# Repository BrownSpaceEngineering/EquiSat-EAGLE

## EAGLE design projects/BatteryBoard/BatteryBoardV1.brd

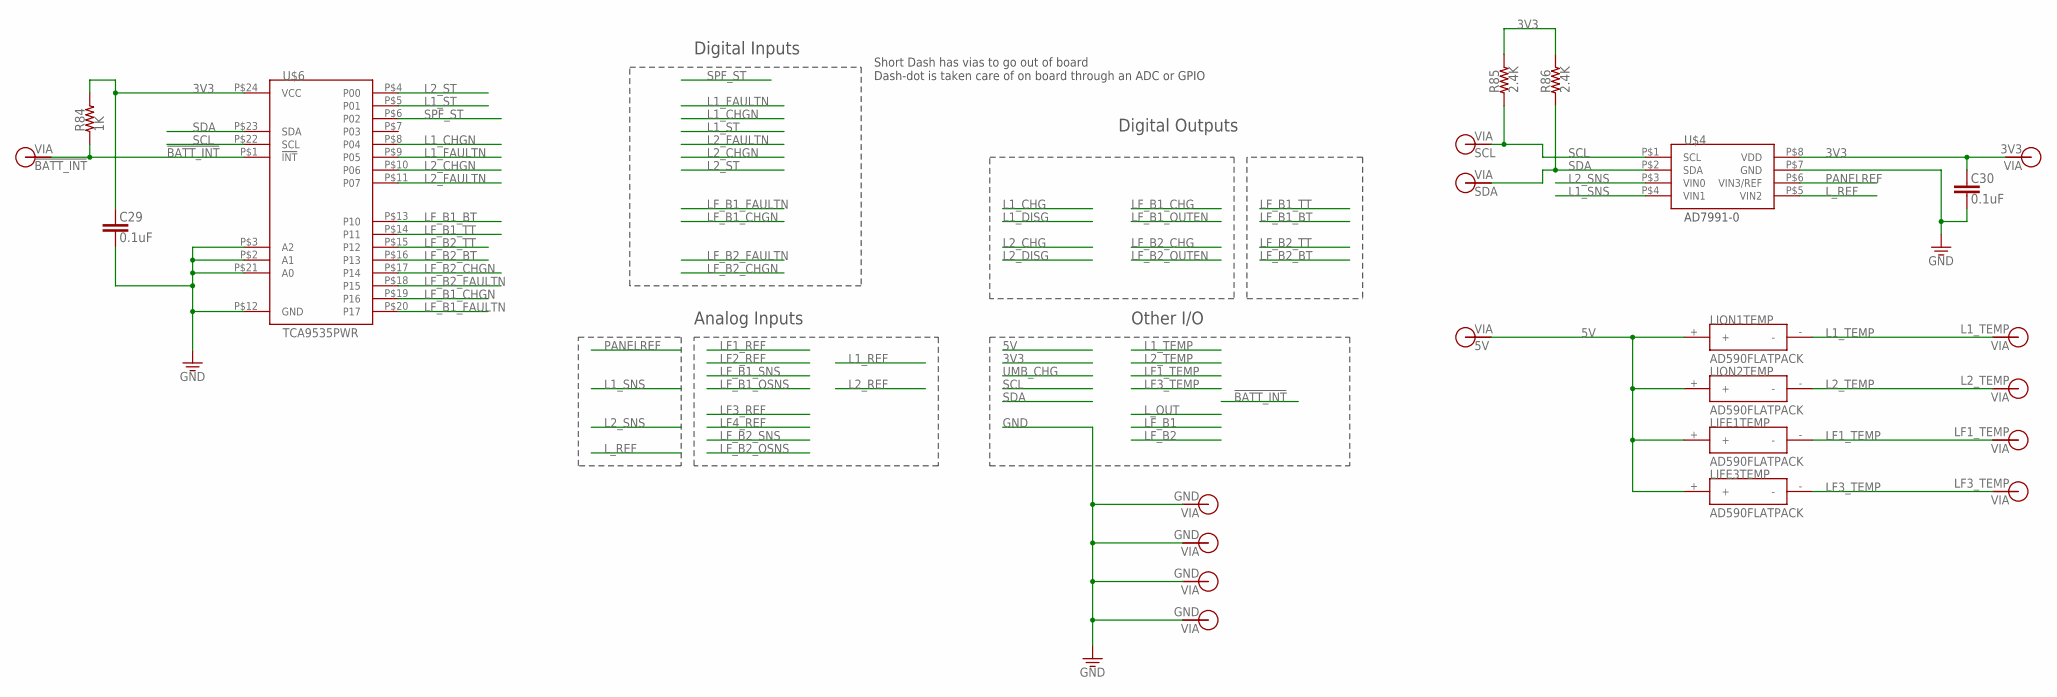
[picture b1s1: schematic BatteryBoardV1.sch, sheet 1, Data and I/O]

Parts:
C29, C30: 0.1uF; 0805
LIFE1TEMP, LIFE3TEMP: AD590FLATPACK; FLATPACK
LION1TEMP, LION2TEMP: AD590FLATPACK; FLATPACK
R84: 1K; 0805
R85, R86: 2.4K; 0805
U$4: AD7991-0; SOT-23-8
U$6: TCA9535PWR; TSSOP-24
V9: 5V; VIA-60MIL
V11: !BATT_INT!; VIA-60MIL
V12: GND; VIA-60MIL-SQ
V13, V22, V23: GND; VIA-120MIL
V24: L1_TEMP; VIA-60MIL
V32: L2_TEMP; VIA-60MIL
V37: LF1_TEMP; VIA-60MIL
V50: LF3_TEMP; VIA-60MIL
V51: 3V3; VIA-60MIL
V52: SCL; VIA-60MIL
V53: SDA; VIA-60MIL

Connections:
3V3: C29.1, C30.1, R84.2, R85.2, R86.2, U$4.P$8 (VDD), U$6.P$24 (VCC), V51.P$1; also elsewhere on the board
5V: LIFE1TEMP.+, LIFE3TEMP.+, LION1TEMP.+, LION2TEMP.+, V9.P$1
!BATT_INT!: R84.1, U$6.P$1 (!INT!), V11.P$1
GND: C29.2, C30.2, U$4.P$7 (GND), U$6.P$2 (A1), U$6.P$3 (A2), U$6.P$12 (GND), U$6.P$21 (A0), V12.P$1, V13.P$1, V22.P$1, V23.P$1; also elsewhere on the board
L1_CHGN: U$6.P$8 (P04); also elsewhere on the board
L1_FAULTN: U$6.P$9 (P05); also elsewhere on the board
L1_SNS: U$4.P$4 (VIN1); also elsewhere on the board
L1_ST: U$6.P$5 (P01); also elsewhere on the board
L1_TEMP: LION1TEMP.-, V24.P$1
L2_CHGN: U$6.P$10 (P06); also elsewhere on the board
L2_FAULTN: U$6.P$11 (P07); also elsewhere on the board
L2_SNS: U$4.P$3 (VIN0); also elsewhere on the board
L2_ST: U$6.P$4 (P00); also elsewhere on the board
L2_TEMP: LION2TEMP.-, V32.P$1
LF1_TEMP: LIFE1TEMP.-, V37.P$1
LF3_TEMP: LIFE3TEMP.-, V50.P$1
LF_B1_BT: U$6.P$13 (P10); also elsewhere on the board
LF_B1_CHGN: U$6.P$19 (P16); also elsewhere on the board
LF_B1_FAULTN: U$6.P$20 (P17); also elsewhere on the board
LF_B1_TT: U$6.P$14 (P11); also elsewhere on the board
LF_B2_BT: U$6.P$16 (P13); also elsewhere on the board
LF_B2_CHGN: U$6.P$17 (P14); also elsewhere on the board
LF_B2_FAULTN: U$6.P$18 (P15); also elsewhere on the board
LF_B2_TT: U$6.P$15 (P12); also elsewhere on the board
L_REF: U$4.P$5 (VIN2); also elsewhere on the board
PANELREF: U$4.P$6 (VIN3/REF); also elsewhere on the board
SCL: R85.1, U$4.P$1 (SCL), U$6.P$22 (SCL), V52.P$1
SDA: R86.1, U$4.P$2 (SDA), U$6.P$23 (SDA), V53.P$1
SPF_ST: U$6.P$6 (P02); also elsewhere on the board

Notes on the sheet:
Digital Inputs
Digital Outputs
Analog Inputs
Other I/O
Short Dash has vias to go out of board Dash-dot is taken care of on board through an ADC or GPIO

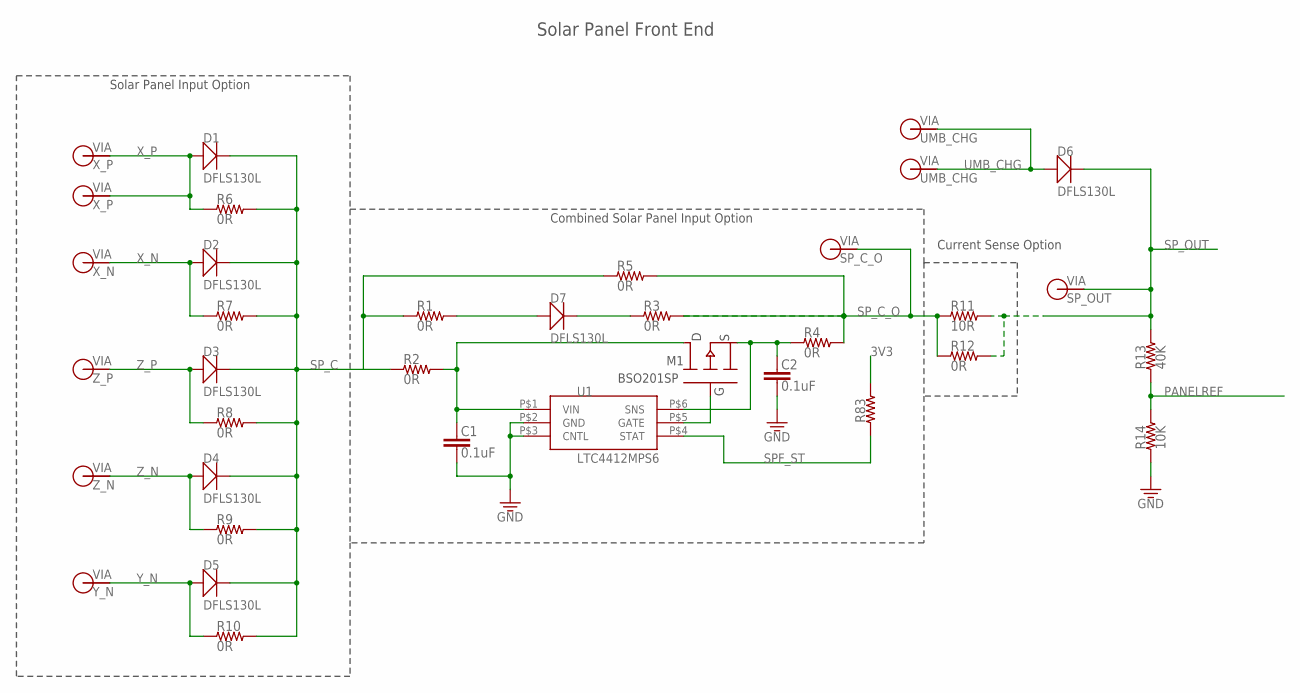
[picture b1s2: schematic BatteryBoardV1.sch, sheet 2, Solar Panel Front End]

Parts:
C1, C2: 0.1uF; 0805
D1, D2, D3, D4, D5, D6, D7: DFLS130L; PWRDI-123
M1: BSO201SP; SO-8
R1, R2, R3, R4, R5, R6, R7, R8, R9, R10, R12: 0R; 0805
R11: 10R; 0805
R13: 40K; 0805
R14: 10K; 0805
R83: RES0805; 0805
U1: LTC4412MPS6; TSOT23-6
V1: UMB_CHG; VIA-60MIL
V2: X_P; VIA-60MIL
V3: X_N; VIA-60MIL
V4: Z_P; VIA-60MIL
V5: Z_N; VIA-60MIL
V6: Y_N; VIA-60MIL
V7: SP_C_O; VIA-60MIL-SQ
V8: SP_OUT; VIA-60MIL-SQ
V39: UMB_CHG; VIA-60MIL-SQ
V49: X_P; VIA-60MIL-SQ

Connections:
3V3: R83.2; also elsewhere on the board
GND: C1.2, C2.2, R14.1, U1.P$2 (GND), U1.P$3 (CNTL); also elsewhere on the board
unnamed: M1.P$4 (G), U1.P$5 (GATE)
unnamed: C2.1, M1.P$1 (S), M1.P$2 (S), M1.P$3 (S), R4.1, U1.P$6 (SNS)
unnamed: D7.A, R1.2
unnamed: D7.C, R3.1
unnamed: C1.1, M1.P$5 (D), M1.P$6 (D), M1.P$7 (D), M1.P$8 (D), R2.2, U1.P$1 (VIN)
PANELREF: R13.1, R14.2; also elsewhere on the board
SPF_ST: R83.1, U1.P$4 (STAT); also elsewhere on the board
SP_C: D1.C, D2.C, D3.C, D4.C, D5.C, R1.1, R2.1, R5.1, R6.2, R7.2, R8.2, R9.2, R10.2
SP_C_O: R3.2, R4.2, R5.2, R11.1, R12.1, V7.P$1
SP_OUT: D6.C, R11.2, R12.2, R13.2, V8.P$1; also elsewhere on the board
UMB_CHG: D6.A, V1.P$1, V39.P$1
X_N: D2.A, R7.1, V3.P$1
X_P: D1.A, R6.1, V2.P$1, V49.P$1
Y_N: D5.A, R10.1, V6.P$1
Z_N: D4.A, R9.1, V5.P$1
Z_P: D3.A, R8.1, V4.P$1

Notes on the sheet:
Solar Panel Input Option
Combined Solar Panel Input Option
Current Sense Option
Solar Panel Front End

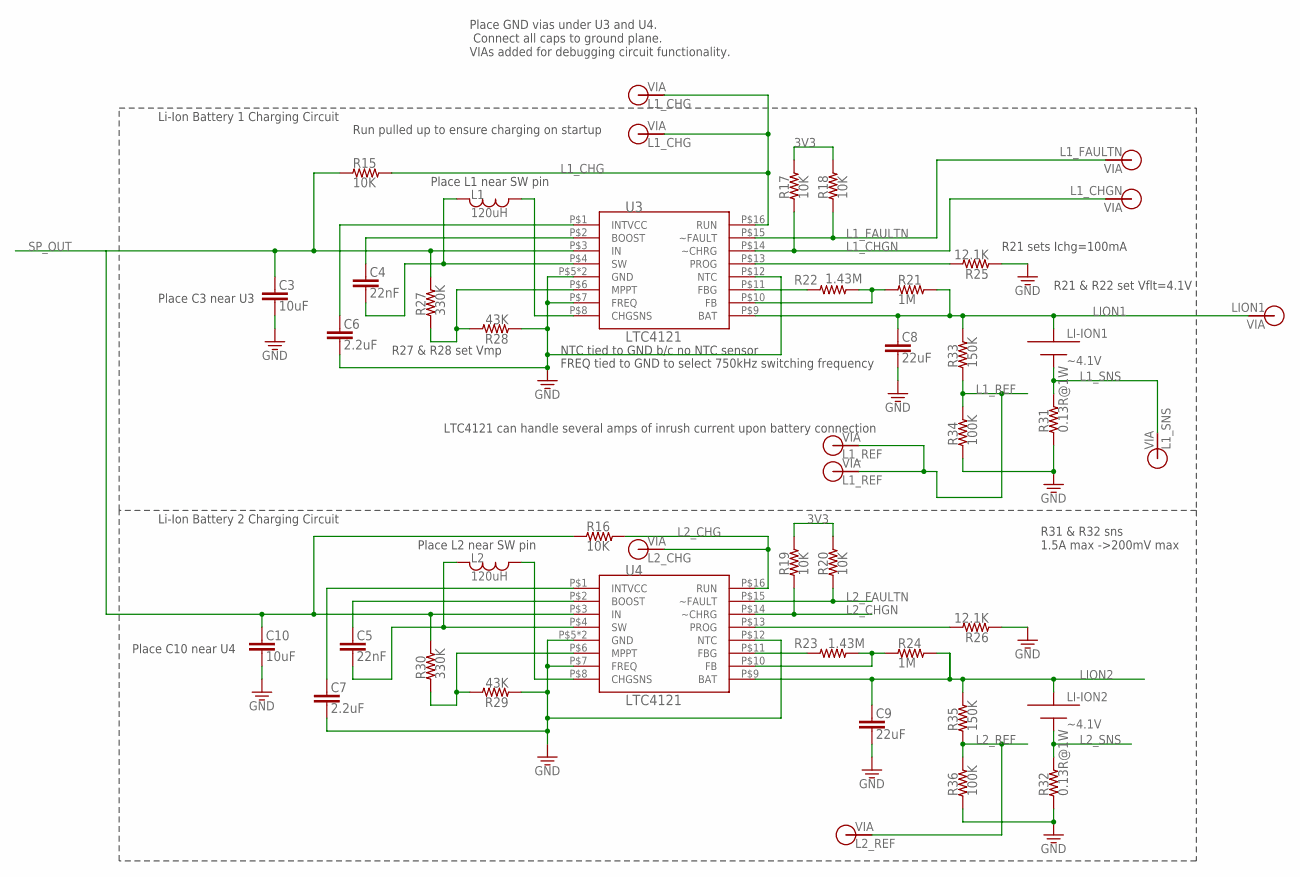
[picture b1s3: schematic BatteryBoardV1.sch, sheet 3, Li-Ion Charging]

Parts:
C3, C10: 10uF; 0805
C4, C5: 22nF; 0805
C6, C7: 2.2uF; 0805
C8, C9: 22uF; 0805
L1, L2: 120uH; 1812
LI-ION1, LI-ION2: ~4.1V; EQUISAT-BATTERY-VA
R15, R16, R17, R18, R19, R20: 10K; 0805
R21, R24: 1M; 0805
R22, R23: 1.43M; 0805
R25, R26: 12.1K; 0805
R27, R30: 330K; 0805
R28, R29: 43K; 0805
R31, R32: 0.13R@1W; 1210
R33, R35: 150K; 0805
R34, R36: 100K; 0805
U3, U4: LTC4121; QFN-16-PAD
V10: L1_CHG; VIA-60MIL
V25: L1_REF; VIA-60MIL
V29: L2_REF; VIA-60MIL
V33: L2_CHG; VIA-60MIL
V40: L1_CHG; VIA-60MIL-SQ
V41: L1_FAULTN; VIA-60MIL-SQ
V42: L1_CHGN; VIA-60MIL-SQ
V43: L1_SNS; VIA-60MIL-SQ
V44: L1_REF; VIA-60MIL-SQ
V45: LION1; VIA-60MIL-SQ

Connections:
3V3: R17.2, R18.2, R19.2, R20.2; also elsewhere on the board
GND: C3.2, C6.2, C7.2, C8.2, C9.2, C10.2, R25.1, R26.1, R28.1, R29.1, R31.P$1 (1), R32.P$1 (1), R34.1, R36.1, U3.P$5 (GND), U3.P$7 (FREQ), U3.P$12 (NTC), U3.P$17 (GND), U4.P$5 (GND), U4.P$7 (FREQ), U4.P$12 (NTC), U4.P$17 (GND); also elsewhere on the board
L1_CHG: R15.2, U3.P$16 (RUN), V10.P$1, V40.P$1
L1_CHGN: R17.1, U3.P$14 (~CHRG), V42.P$1; also elsewhere on the board
L1_FAULTN: R18.1, U3.P$15 (~FAULT), V41.P$1; also elsewhere on the board
L1_REF: R33.1, R34.2, V25.P$1, V44.P$1
L1_SNS: LI-ION1.MINUS, R31.P$2 (2), V43.P$1; also elsewhere on the board
L2_CHG: R16.2, U4.P$16 (RUN), V33.P$1
L2_CHGN: R19.1, U4.P$14 (~CHRG); also elsewhere on the board
L2_FAULTN: R20.1, U4.P$15 (~FAULT); also elsewhere on the board
L2_REF: R35.1, R36.2, V29.P$1
L2_SNS: LI-ION2.MINUS, R32.P$2 (2); also elsewhere on the board
LION1: C8.1, LI-ION1.PLUS, R21.2, R33.2, U3.P$9 (BAT), V45.P$1; also elsewhere on the board
LION2: C9.1, LI-ION2.PLUS, R24.2, R35.2, U4.P$9 (BAT); also elsewhere on the board
unnamed: C4.2, L1.P$1, U3.P$4 (SW)
unnamed: C4.1, U3.P$2 (BOOST)
unnamed: C5.1, U4.P$2 (BOOST)
unnamed: C5.2, L2.P$1, U4.P$4 (SW)
unnamed: C7.1, U4.P$1 (INTVCC)
unnamed: C6.1, U3.P$1 (INTVCC)
unnamed: R23.1, U4.P$11 (FBG)
unnamed: R23.2, R24.1, U4.P$10 (FB)
unnamed: R22.1, U3.P$11 (FBG)
unnamed: R21.1, R22.2, U3.P$10 (FB)
unnamed: L1.P$2, U3.P$8 (CHGSNS)
unnamed: R25.2, U3.P$13 (PROG)
unnamed: R26.2, U4.P$13 (PROG)
unnamed: R29.2, R30.1, U4.P$6 (MPPT)
unnamed: R27.1, R28.2, U3.P$6 (MPPT)
unnamed: L2.P$2, U4.P$8 (CHGSNS)
SP_OUT: C3.1, C10.1, R15.1, R16.1, R27.2, R30.2, U3.P$3 (IN), U4.P$3 (IN); also elsewhere on the board

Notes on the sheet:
FREQ tied to GND to select 750kHz switching frequency
R21 sets Ichg=100mA
R21 & R22 set Vflt=4.1V
R27 & R28 set Vmp
Place C3 near U3
Place C10 near U4
Place L2 near SW pin
Place L1 near SW pin
Place GND vias under U3 and U4. Connect all caps to ground plane. VIAs added for debugging circuit functionality.
Li-Ion Battery 1 Charging Circuit
Li-Ion Battery 2 Charging Circuit
Run pulled up to ensure charging on startup
NTC tied to GND b/c no NTC sensor
R31 & R32 sns 1.5A max ->200mV max
LTC4121 can handle several amps of inrush current upon battery connection

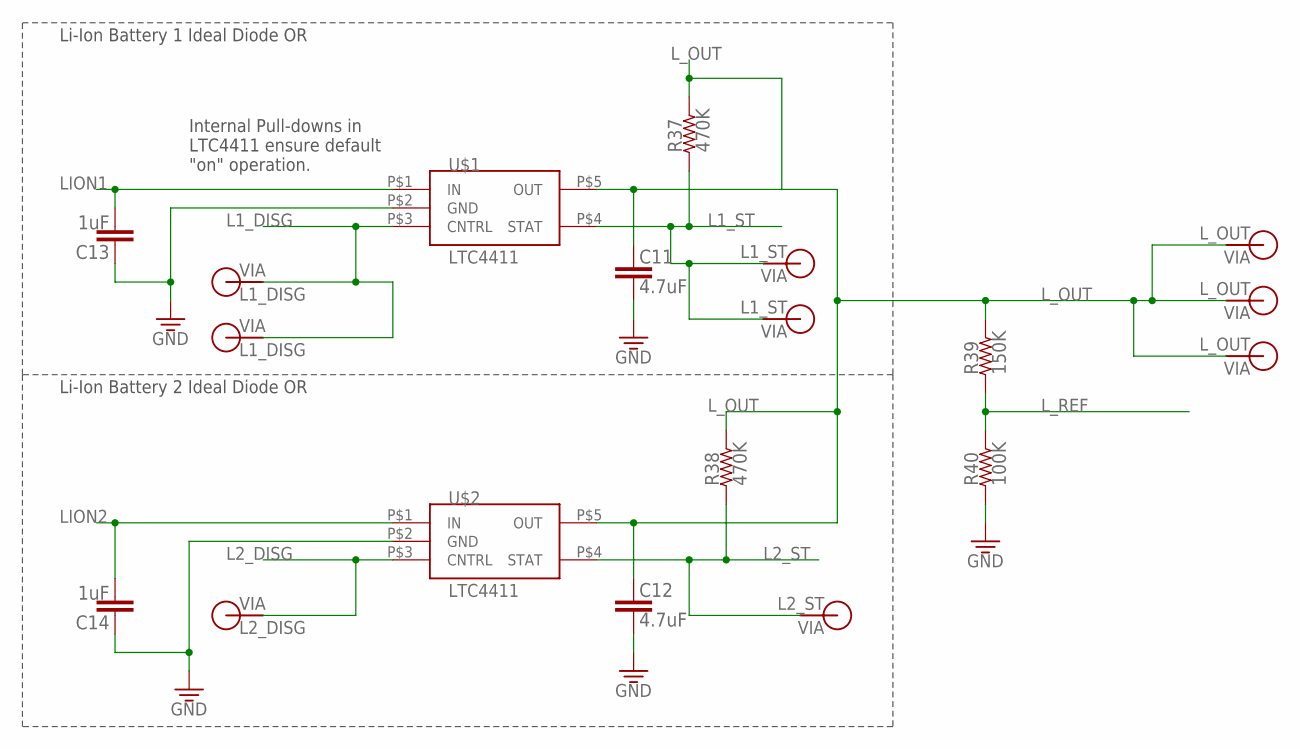
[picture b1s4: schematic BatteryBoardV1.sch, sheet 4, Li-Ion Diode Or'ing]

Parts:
C11, C12: 4.7uF; 0805
C13, C14: 1uF; 0805
R37, R38: 470K; 0805
R39: 150K; 0805
R40: 100K; 0805
U$1, U$2: LTC4411; TSOT23-5
V30, V54: L_OUT; VIA-120MIL
V34: L1_DISG; VIA-60MIL
V35: L2_DISG; VIA-60MIL
V36: L1_ST; VIA-60MIL
V38: L2_ST; VIA-60MIL
V46: L1_DISG; VIA-60MIL-SQ
V47: L1_ST; VIA-60MIL-SQ
V48: L_OUT; VIA-60MIL-SQ

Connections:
GND: C11.2, C12.2, C13.1, C14.1, R40.1, U$1.P$2 (GND), U$2.P$2 (GND); also elsewhere on the board
L1_DISG: U$1.P$3 (CNTRL), V34.P$1, V46.P$1
L1_ST: R37.1, U$1.P$4 (STAT), V36.P$1, V47.P$1; also elsewhere on the board
L2_DISG: U$2.P$3 (CNTRL), V35.P$1
L2_ST: R38.1, U$2.P$4 (STAT), V38.P$1; also elsewhere on the board
LION1: C13.2, U$1.P$1 (IN); also elsewhere on the board
LION2: C14.2, U$2.P$1 (IN); also elsewhere on the board
L_OUT: C11.1, C12.1, R37.2, R38.2, R39.2, U$1.P$5 (OUT), U$2.P$5 (OUT), V30.P$1, V48.P$1, V54.P$1
L_REF: R39.1, R40.2; also elsewhere on the board

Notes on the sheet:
Internal Pull-downs in LTC4411 ensure default "on" operation.
Li-Ion Battery 1 Ideal Diode OR
Li-Ion Battery 2 Ideal Diode OR

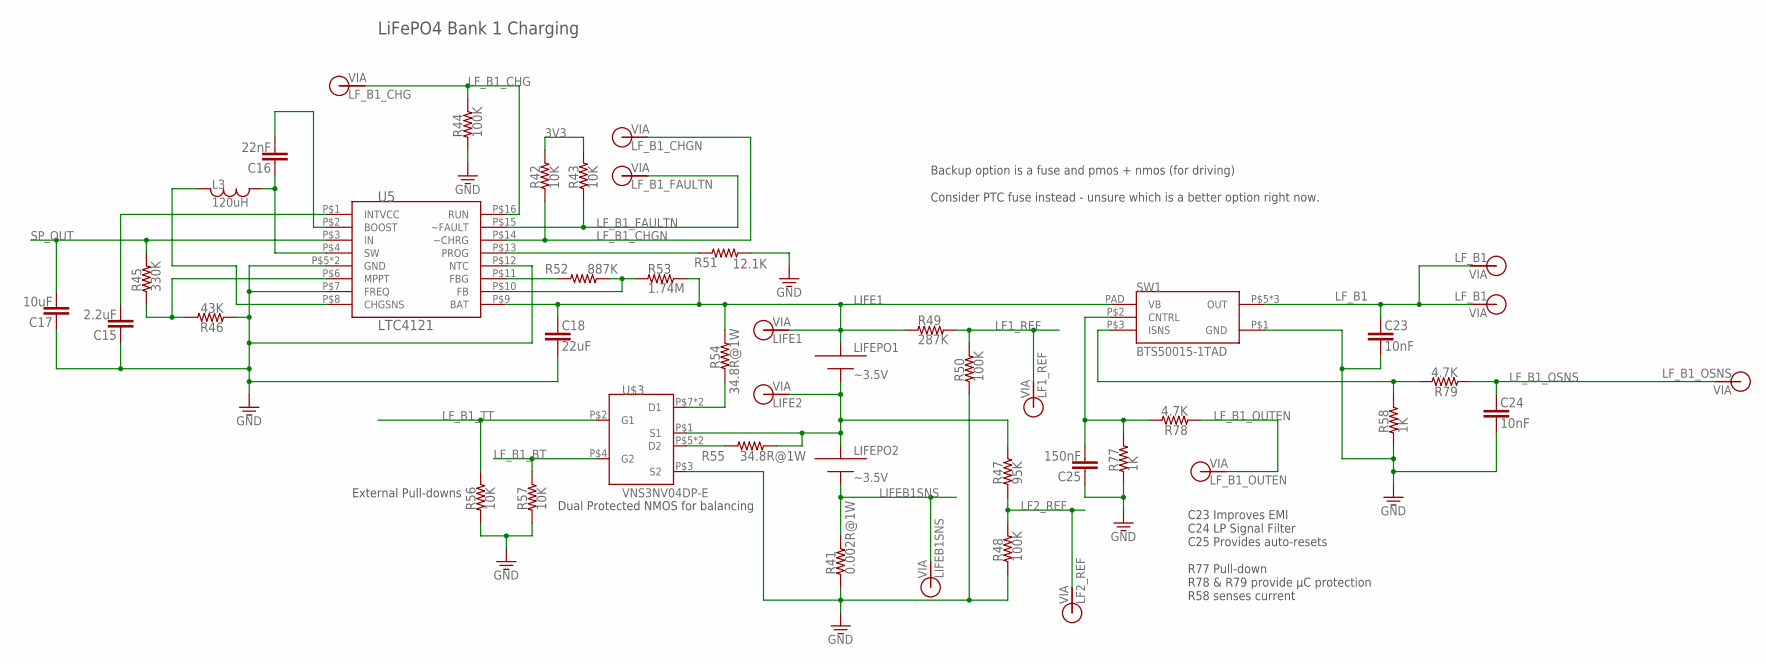
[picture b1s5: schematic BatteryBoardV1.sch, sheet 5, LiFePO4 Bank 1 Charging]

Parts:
C15: 2.2uF; 0805
C16: 22nF; 0805
C17: 10uF; 0805
C18: 22uF; 0805
C23, C24: 10nF; 0805
C25: 150nF; 0805
L3: 120uH; 1812
LIFEPO1: ~3.5V; EQUISAT-BATTERY-VA
LIFEPO2: ~3.5V; EQUISAT-BATTERY-VB
R41: 0.002R@1W; 1210
R42, R43, R56, R57: 10K; 0805
R44, R48, R50: 100K; 0805
R45: 330K; 0805
R46: 43K; 0805
R47: 95K; 0805
R49: 287K; 0805
R51: 12.1K; 0805
R52: 887K; 0805
R53: 1.74M; 0805
R54, R55: 34.8R@1W; 1210
R58, R77: 1K; 0805
R78, R79: 4.7K; 0805
SW1: BTS50015-1TAD; TO-263-7-8
U5: LTC4121; QFN-16-PAD
U$3: VNS3NV04DP-E; SO-8
V14: LIFEB1SNS; VIA-60MIL
V15: LF_B1_CHG; VIA-60MIL
V16: LIFE2; VIA-60MIL-SQ
V17: LIFE1; VIA-60MIL-SQ
V18: LF_B1_CHGN; VIA-60MIL
V19: LF_B1_FAULTN; VIA-60MIL
V20: LF_B1_OUTEN; VIA-60MIL
V21, V26: LF_B1; VIA-120MIL
V31: LF_B1_OSNS; VIA-60MIL
V58: LF1_REF; VIA-60MIL
V59: LF2_REF; VIA-60MIL

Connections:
3V3: R42.2, R43.2; also elsewhere on the board
GND: C15.1, C17.1, C18.2, C23.2, C24.2, C25.1, R41.P$1 (1), R44.1, R46.1, R48.1, R50.1, R51.2, R56.1, R57.1, R58.1, R77.1, SW1.P$1 (GND), U5.P$5 (GND), U5.P$7 (FREQ), U5.P$12 (NTC), U5.P$17 (GND), U$3.P$3 (S2); also elsewhere on the board
LF1_REF: R49.2, R50.2, V58.P$1
LF2_REF: R47.1, R48.2, V59.P$1
LF_B1: C23.1, SW1.P$5 (OUT), SW1.P$6 (OUT), SW1.P$7 (OUT), V21.P$1, V26.P$1
LF_B1_BT: R57.2, U$3.P$4 (G2); also elsewhere on the board
LF_B1_CHG: R44.2, U5.P$16 (RUN), V15.P$1
LF_B1_CHGN: R42.1, U5.P$14 (~CHRG), V18.P$1; also elsewhere on the board
LF_B1_FAULTN: R43.1, U5.P$15 (~FAULT), V19.P$1; also elsewhere on the board
LF_B1_OSNS: C24.1, R79.1, V31.P$1
LF_B1_OUTEN: R78.1, V20.P$1
LF_B1_TT: R56.2, U$3.P$2 (G1); also elsewhere on the board
LIFE1: C18.1, LIFEPO1.PLUS, R49.1, R53.2, R54.P$2 (2), SW1.PAD (VB), U5.P$9 (BAT), V17.P$1
LIFE2: LIFEPO1.MINUS, LIFEPO2.PLUS, R47.2, R55.P$1 (1), U$3.P$1 (S1), V16.P$1
LIFEB1SNS: LIFEPO2.MINUS, R41.P$2 (2), V14.P$1
unnamed: R51.1, U5.P$13 (PROG)
unnamed: R54.P$1 (1), U$3.P$7 (D1), U$3.P$8 (D1)
unnamed: R55.P$2 (2), U$3.P$5 (D2), U$3.P$6 (D2)
unnamed: R52.1, U5.P$11 (FBG)
unnamed: R45.1, R46.2, U5.P$6 (MPPT)
unnamed: R52.2, R53.1, U5.P$10 (FB)
unnamed: C15.2, U5.P$1 (INTVCC)
unnamed: C16.1, L3.P$2, U5.P$4 (SW)
unnamed: C16.2, U5.P$2 (BOOST)
unnamed: L3.P$1, U5.P$8 (CHGSNS)
unnamed: C25.2, R77.2, R78.2, SW1.P$2 (CNTRL)
unnamed: R58.2, R79.2, SW1.P$3 (ISNS)
SP_OUT: C17.2, R45.2, U5.P$3 (IN); also elsewhere on the board

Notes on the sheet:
LiFePO4 Bank 1 Charging
External Pull-downs
Dual Protected NMOS for balancing
Backup option is a fuse and pmos + nmos (for driving) Consider PTC fuse instead - unsure which is a better option right now.
C23 Improves EMI C24 LP Signal Filter C25 Provides auto-resets R77 Pull-down R78 & R79 provide µC protection R58 senses current

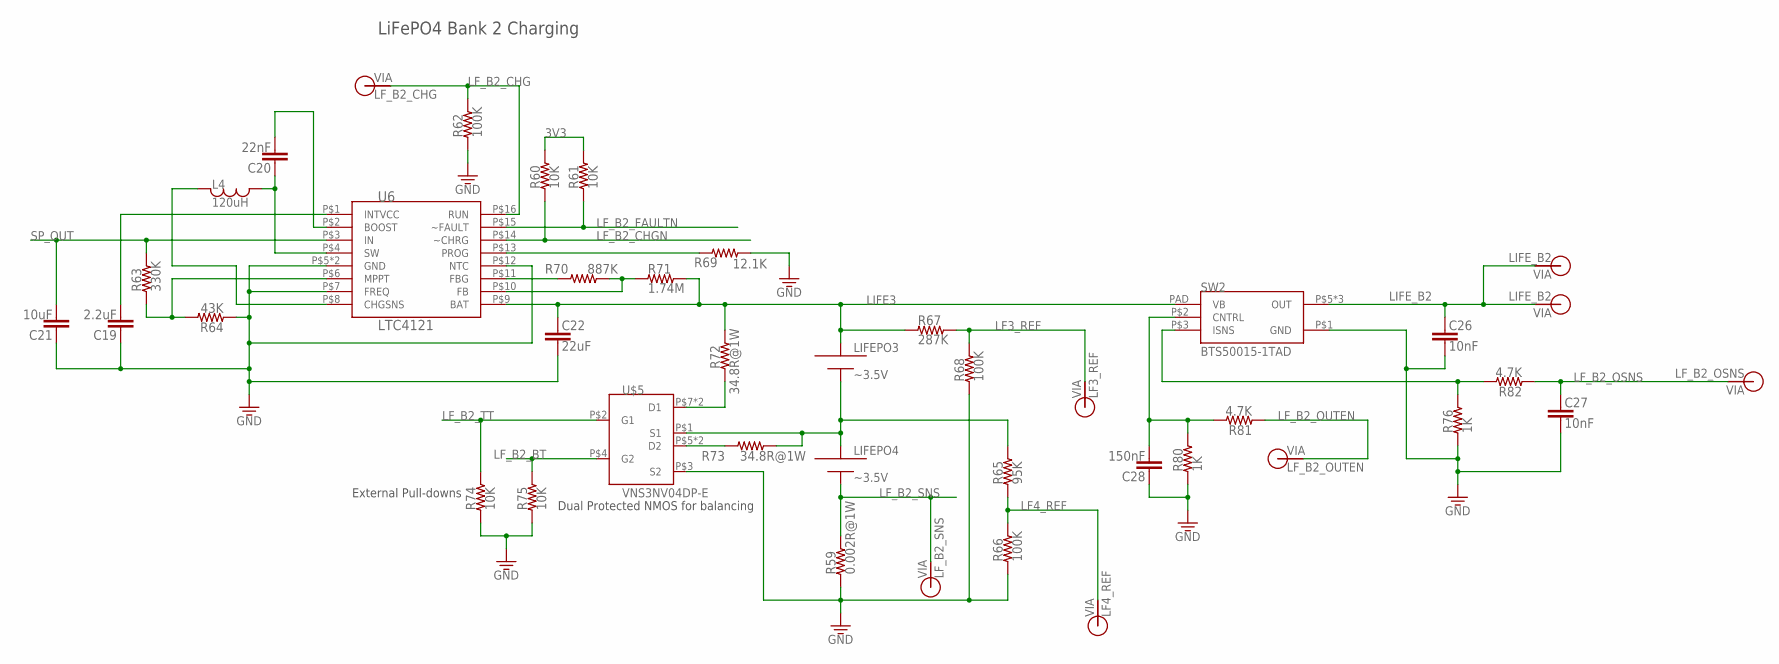
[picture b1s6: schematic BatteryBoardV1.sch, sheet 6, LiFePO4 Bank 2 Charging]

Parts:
C19: 2.2uF; 0805
C20: 22nF; 0805
C21: 10uF; 0805
C22: 22uF; 0805
C26, C27: 10nF; 0805
C28: 150nF; 0805
L4: 120uH; 1812
LIFEPO3: ~3.5V; EQUISAT-BATTERY-VA
LIFEPO4: ~3.5V; EQUISAT-BATTERY-VB
R59: 0.002R@1W; 1210
R60, R61, R74, R75: 10K; 0805
R62, R66, R68: 100K; 0805
R63: 330K; 0805
R64: 43K; 0805
R65: 95K; 0805
R67: 287K; 0805
R69: 12.1K; 0805
R70: 887K; 0805
R71: 1.74M; 0805
R72, R73: 34.8R@1W; 1210
R76, R80: 1K; 0805
R81, R82: 4.7K; 0805
SW2: BTS50015-1TAD; TO-263-7-8
U6: LTC4121; QFN-16-PAD
U$5: VNS3NV04DP-E; SO-8
V27, V28: LIFE_B2; VIA-120MIL
V56: LF_B2_OUTEN; VIA-60MIL
V57: LF_B2_CHG; VIA-60MIL
V60: LF_B2_SNS; VIA-60MIL
V61: LF4_REF; VIA-60MIL
V62: LF3_REF; VIA-60MIL
V63: LF_B2_OSNS; VIA-60MIL

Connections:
3V3: R60.2, R61.2; also elsewhere on the board
GND: C19.1, C21.1, C22.2, C26.2, C27.2, C28.1, R59.P$1 (1), R62.1, R64.1, R66.1, R68.1, R69.2, R74.1, R75.1, R76.1, R80.1, SW2.P$1 (GND), U6.P$5 (GND), U6.P$7 (FREQ), U6.P$12 (NTC), U6.P$17 (GND), U$5.P$3 (S2); also elsewhere on the board
LF3_REF: R67.2, R68.2, V62.P$1
LF4_REF: R65.1, R66.2, V61.P$1
LF_B2_BT: R75.2, U$5.P$4 (G2); also elsewhere on the board
LF_B2_CHG: R62.2, U6.P$16 (RUN), V57.P$1
LF_B2_CHGN: R60.1, U6.P$14 (~CHRG); also elsewhere on the board
LF_B2_FAULTN: R61.1, U6.P$15 (~FAULT); also elsewhere on the board
LF_B2_OSNS: C27.1, R82.1, V63.P$1
LF_B2_OUTEN: R81.1, V56.P$1
LF_B2_SNS: LIFEPO4.MINUS, R59.P$2 (2), V60.P$1
LF_B2_TT: R74.2, U$5.P$2 (G1); also elsewhere on the board
LIFE3: C22.1, LIFEPO3.PLUS, R67.1, R71.2, R72.P$2 (2), SW2.PAD (VB), U6.P$9 (BAT)
LIFE4: LIFEPO3.MINUS, LIFEPO4.PLUS, R65.2, R73.P$1 (1), U$5.P$1 (S1)
LIFE_B2: C26.1, SW2.P$5 (OUT), SW2.P$6 (OUT), SW2.P$7 (OUT), V27.P$1, V28.P$1
unnamed: R63.1, R64.2, U6.P$6 (MPPT)
unnamed: R69.1, U6.P$13 (PROG)
unnamed: R70.1, U6.P$11 (FBG)
unnamed: R70.2, R71.1, U6.P$10 (FB)
unnamed: C19.2, U6.P$1 (INTVCC)
unnamed: C20.1, L4.P$2, U6.P$4 (SW)
unnamed: C20.2, U6.P$2 (BOOST)
unnamed: L4.P$1, U6.P$8 (CHGSNS)
unnamed: R72.P$1 (1), U$5.P$7 (D1), U$5.P$8 (D1)
unnamed: R73.P$2 (2), U$5.P$5 (D2), U$5.P$6 (D2)
unnamed: R76.2, R82.2, SW2.P$3 (ISNS)
unnamed: C28.2, R80.2, R81.2, SW2.P$2 (CNTRL)
SP_OUT: C21.2, R63.2, U6.P$3 (IN); also elsewhere on the board

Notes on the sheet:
LiFePO4 Bank 2 Charging
External Pull-downs
Dual Protected NMOS for balancing

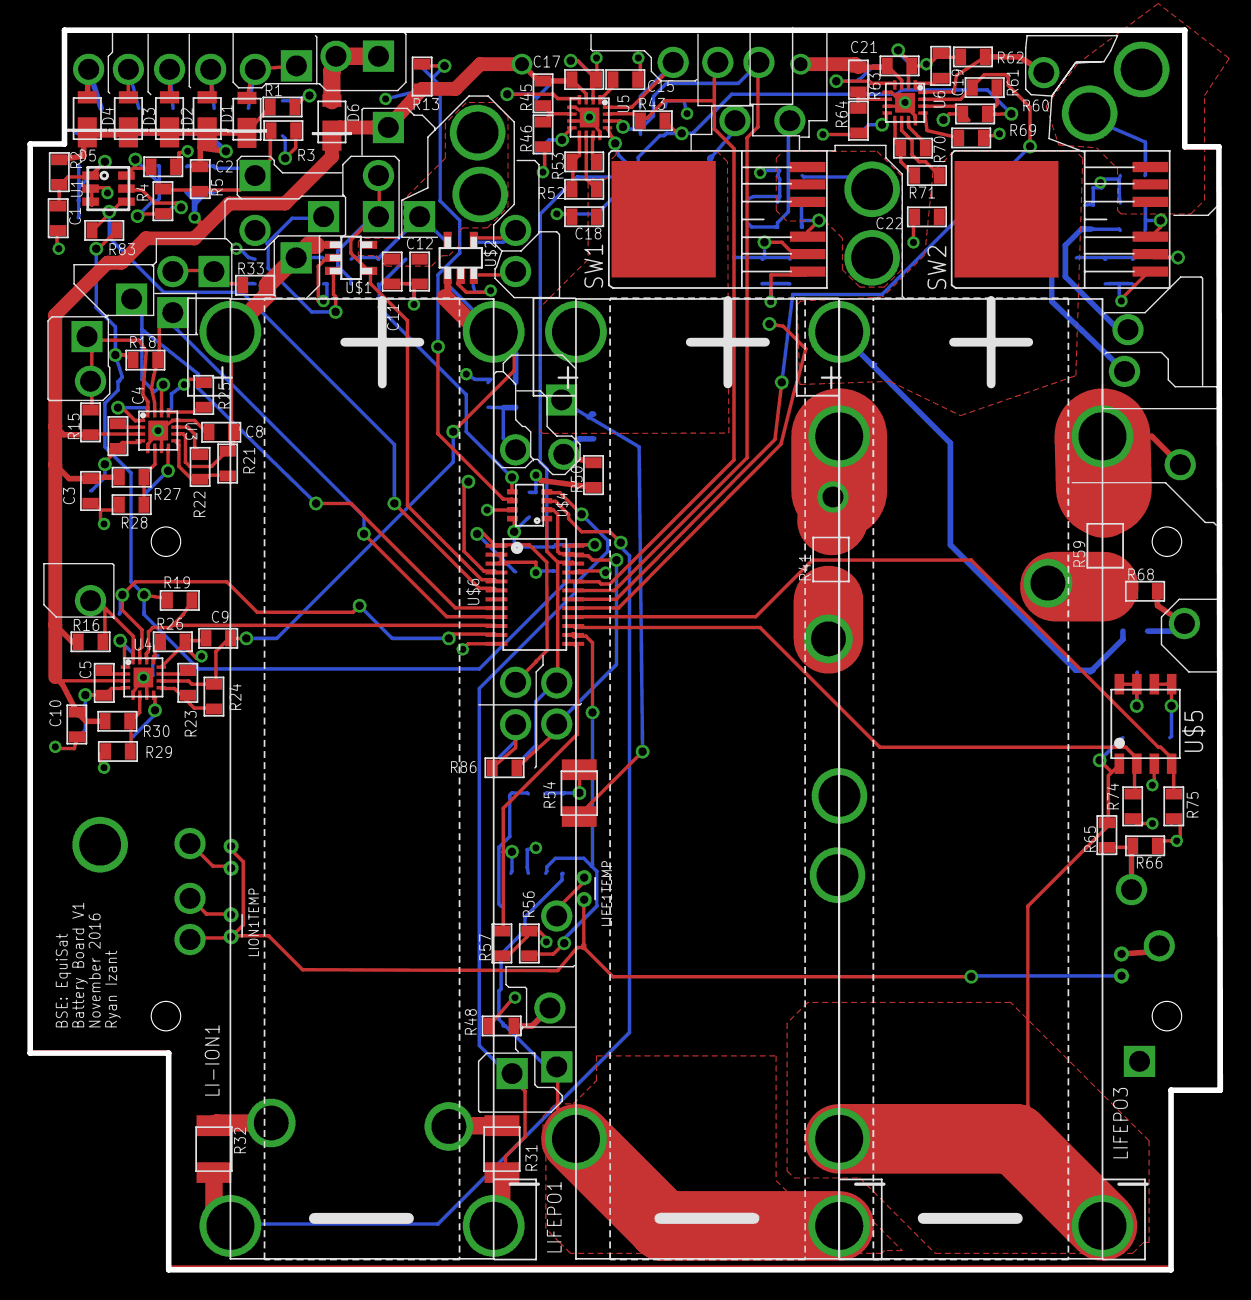
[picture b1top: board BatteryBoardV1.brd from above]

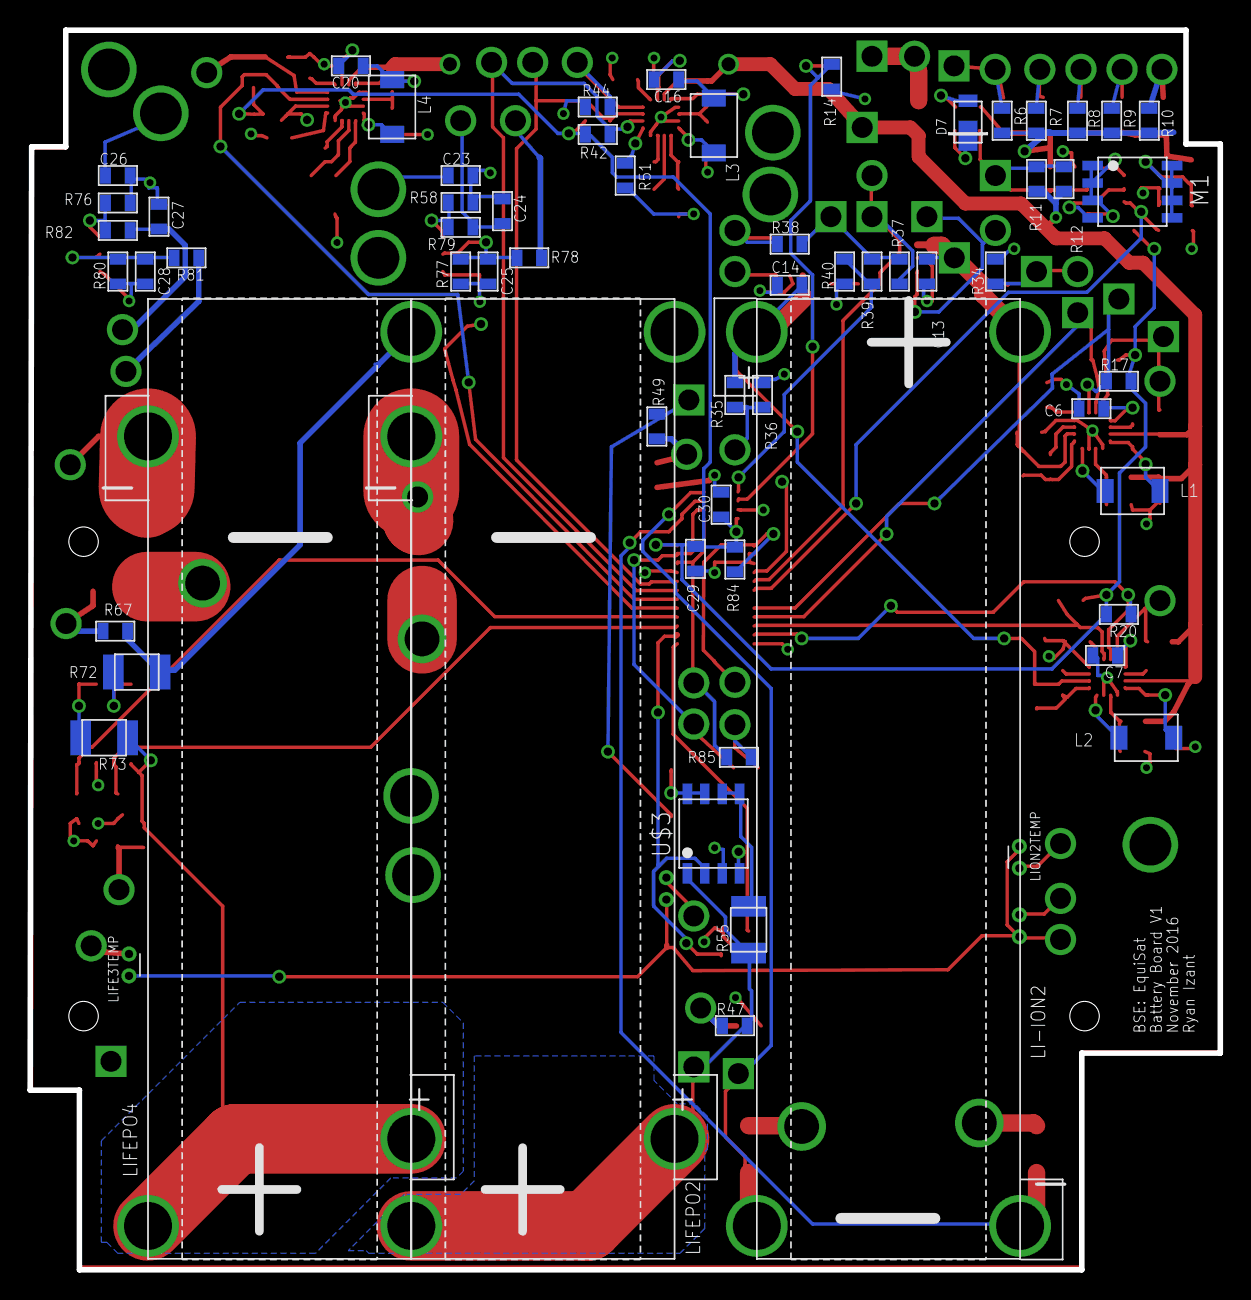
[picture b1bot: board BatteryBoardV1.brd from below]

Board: 4 copper layers, 86.8 x 90.4 mm, 213 parts (62 on the bottom side), 110 nets.

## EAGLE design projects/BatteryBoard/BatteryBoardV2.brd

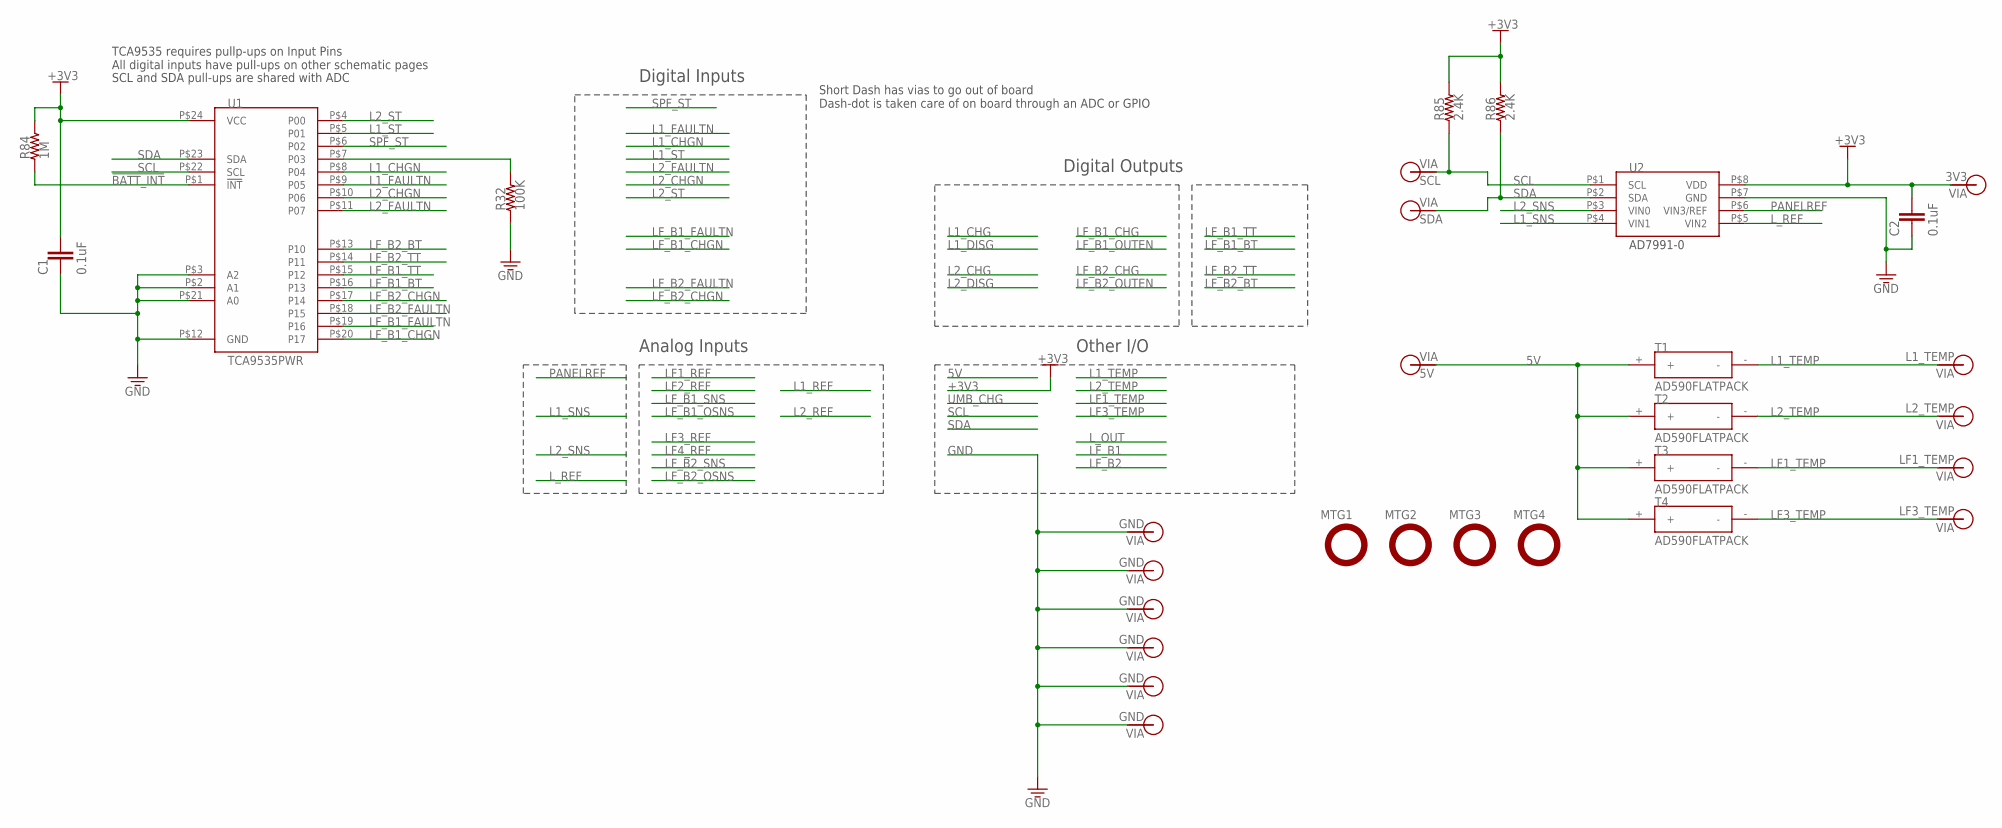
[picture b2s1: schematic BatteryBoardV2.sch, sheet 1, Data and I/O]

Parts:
C1, C2: 0.1uF; 0805
MTG1, MTG2, MTG3, MTG4: MTG-NPTH-#2-CLOSE; #2-CLOSE-NPTH
R32: 100K; 0805
R84: 1M; 0805
R85, R86: 2.4K; 0805
T1, T2, T3, T4: AD590FLATPACK; FLATPACK
U1: TCA9535PWR; TSSOP-24
U2: AD7991-0; SOT-23-8
V1, V2, V4: GND; VIA-120MIL
V3, V28, V36: GND; VIA-60MIL-SQ
V5: SCL; VIA-60MIL
V6: SDA; VIA-60MIL
V7: 5V; VIA-60MIL
V8: L1_TEMP; VIA-60MIL
V9: L2_TEMP; VIA-60MIL
V10: LF1_TEMP; VIA-60MIL
V11: LF3_TEMP; VIA-60MIL
V12: 3V3; VIA-60MIL

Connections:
5V: T1.+, T2.+, T3.+, T4.+, V7.P$1
!BATT_INT!: R84.1, U1.P$1 (!INT!)
+3V3: C1.1, C2.1, R84.2, R85.2, R86.2, U1.P$24 (VCC), U2.P$8 (VDD), V12.P$1; also elsewhere on the board
GND: C1.2, C2.2, R32.1, U1.P$2 (A1), U1.P$3 (A2), U1.P$12 (GND), U1.P$21 (A0), U2.P$7 (GND), V1.P$1, V2.P$1, V3.P$1, V4.P$1, V28.P$1, V36.P$1; also elsewhere on the board
L1_CHGN: U1.P$8 (P04); also elsewhere on the board
L1_FAULTN: U1.P$9 (P05); also elsewhere on the board
L1_SNS: U2.P$4 (VIN1); also elsewhere on the board
L1_ST: U1.P$5 (P01); also elsewhere on the board
L1_TEMP: T1.-, V8.P$1
L2_CHGN: U1.P$10 (P06); also elsewhere on the board
L2_FAULTN: U1.P$11 (P07); also elsewhere on the board
L2_SNS: U2.P$3 (VIN0); also elsewhere on the board
L2_ST: U1.P$4 (P00); also elsewhere on the board
L2_TEMP: T2.-, V9.P$1
LF1_TEMP: T3.-, V10.P$1
LF3_TEMP: T4.-, V11.P$1
LF_B1_BT: U1.P$16 (P13); also elsewhere on the board
LF_B1_CHGN: U1.P$20 (P17); also elsewhere on the board
LF_B1_FAULTN: U1.P$19 (P16); also elsewhere on the board
LF_B1_TT: U1.P$15 (P12); also elsewhere on the board
LF_B2_BT: U1.P$13 (P10); also elsewhere on the board
LF_B2_CHGN: U1.P$17 (P14); also elsewhere on the board
LF_B2_FAULTN: U1.P$18 (P15); also elsewhere on the board
LF_B2_TT: U1.P$14 (P11); also elsewhere on the board
L_REF: U2.P$5 (VIN2); also elsewhere on the board
unnamed: R32.2, U1.P$7 (P03)
PANELREF: U2.P$6 (VIN3/REF); also elsewhere on the board
SCL: R85.1, U1.P$22 (SCL), U2.P$1 (SCL), V5.P$1
SDA: R86.1, U1.P$23 (SDA), U2.P$2 (SDA), V6.P$1
SPF_ST: U1.P$6 (P02); also elsewhere on the board

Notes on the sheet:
Digital Inputs
Digital Outputs
Analog Inputs
Other I/O
Short Dash has vias to go out of board Dash-dot is taken care of on board through an ADC or GPIO
SCL and SDA pull-ups are shared with ADC
TCA9535 requires pullp-ups on Input Pins All digital inputs have pull-ups on other schematic pages

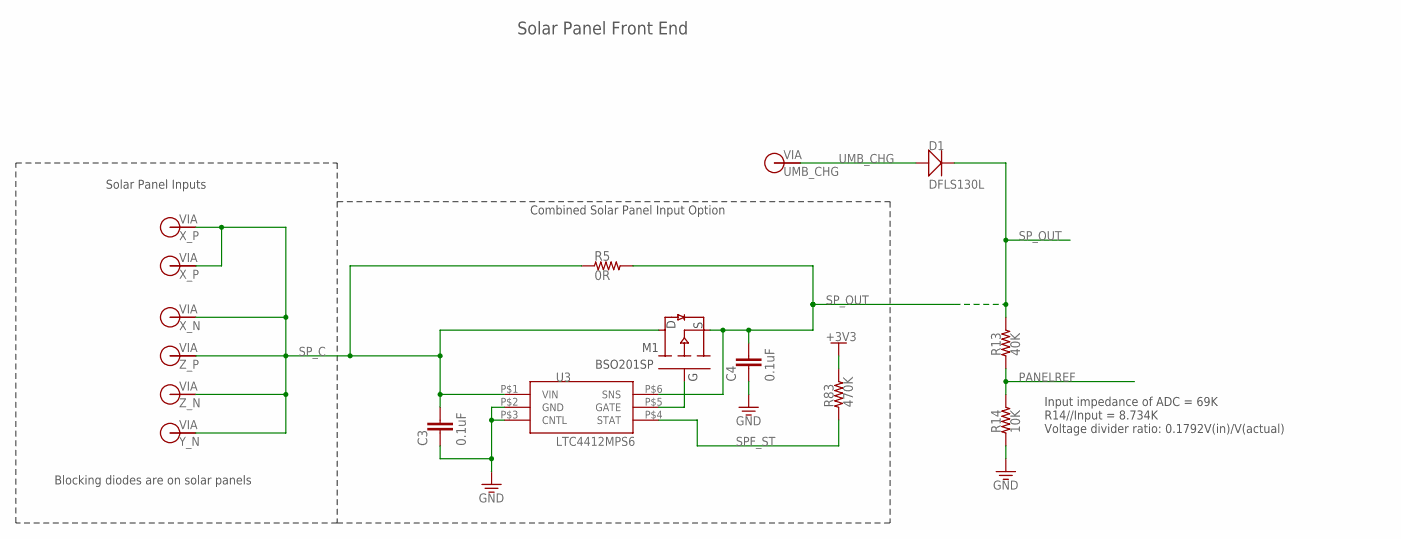
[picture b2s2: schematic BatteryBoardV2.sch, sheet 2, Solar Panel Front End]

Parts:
C3, C4: 0.1uF; 0805
D1: DFLS130L; PWRDI-123
M1: BSO201SP; SO-8
R5: 0R; 0805
R13: 40K; 0805
R14: 10K; 0805
R83: 470K; 0805
U3: LTC4412MPS6; TSOT23-6
V13: X_P; VIA-60MIL
V14: X_P; VIA-60MIL-SQ
V15: X_N; VIA-60MIL
V16: Z_P; VIA-60MIL
V17: Z_N; VIA-60MIL
V18: Y_N; VIA-60MIL
V19: UMB_CHG; VIA-60MIL

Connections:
+3V3: R83.2; also elsewhere on the board
GND: C3.2, C4.2, R14.1, U3.P$2 (GND), U3.P$3 (CNTL); also elsewhere on the board
unnamed: M1.P$4 (G), U3.P$5 (GATE)
PANELREF: R13.1, R14.2; also elsewhere on the board
SPF_ST: R83.1, U3.P$4 (STAT); also elsewhere on the board
SP_C: C3.1, M1.P$5 (D), M1.P$6 (D), M1.P$7 (D), M1.P$8 (D), R5.1, U3.P$1 (VIN), V13.P$1, V14.P$1, V15.P$1, V16.P$1, V17.P$1, V18.P$1
SP_OUT: C4.1, D1.C, M1.P$1 (S), M1.P$2 (S), M1.P$3 (S), R5.2, R13.2, U3.P$6 (SNS); also elsewhere on the board
UMB_CHG: D1.A, V19.P$1

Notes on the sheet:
Solar Panel Inputs
Combined Solar Panel Input Option
Solar Panel Front End
Blocking diodes are on solar panels
Input impedance of ADC = 69K R14//Input = 8.734K Voltage divider ratio: 0.1792V(in)/V(actual)
